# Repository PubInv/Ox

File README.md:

# NASA-COG

## Final Report

The final report delivered to NASA for this project can be [read here](https://drive.google.com/file/d/1jfJcSLfsybuC49I7llPhfTNI8ucRUW3h/view?usp=sharing).

## Introduction

This is a repo for a control system made for NASA to drive a Ceramic Oxygen Generation
technology they have developed. It was forked from ["The Ox"]() project of Public Invention run by Mr. Ben Coombs, which was in turn a fork of the VentOS project of Helpful Engineering let my Ben Coombs, Dr. Erich Schulz, and Robert L. Read.

However, the main reason we are starting with this fork is not that the Pressure Swing
Adsorption system of the Ox is a particularly relevant, but rather that the code
represents a nice platform of simple microcontroller control of related machines.

To wit, includes PlatformIO configuration, a state machine (finite automata),
a superloop architecutre, and a hardware abstraction layer.

This particular project of NASA will improve life support technology in space,
but may eventually greatly improve global health.

An unlisted [YouTube video](https://youtu.be/1nq-Mw7jZ5A) has been uploaded that shows this work in progress as of September, 2022.

## How to run

### Linux
The fundamental way to run this is to perform:  
> cd firmware  
> pio run -e native && ./.pio/build/native/program  
We are currently creating the [RibbonFish](https://github.com/PubInv/NASA-COG/blob/develop/RibbonFish.md) proof-of-concept.
This can be run on a Due by executing:  
> make pio-run-due_ribbonfish  
As this develops, it will use a specific Due hardware configuration,  
please see the [documentation](https://github.com/PubInv/NASA-COG/blob/develop/RibbonFish.md) for details to build your own.  

### Windows
With Visual Studio Code.  
Install the Plateform IO extention  
To open he project in Visual Studio Code.  
Open Project. Navigate to the firmware folder.   
Select the file platformio.ini  

## Annoyances

AFAIK, PlatformIO forces a directory tree depth of 5 levels.

This is not enough to organize the Hardware Abstraction Level they way I would prefer, forcing us to make some messy directories that are less than clear.

For example, to implement a Temperature Sensor, we would ideally have an
abstract (or virtual) implementation, a folder for real hardware,
and a folder for mock sensors.  I have no choice now but to jam
the mock sensors into the same directory with the real hardware and
use a naming convnention.

## The Command System

The NASA-COG system needs to allow the user to enter commands. The most obvious of these is "turn off".
Because the system should avoid thermal shocks, this is actually not simple.

We have previously used an [approach](https://github.com/PubInv/PIRCS-pubinv-respiration-control-standard) of using simple JSON objects to represent commands. We propose to use the same idea here, but obviously,
the command will be custom to the NASA-COG.

### Parameter Setting Commands
The general scheme is to use a JSON object like:

```JavaScript
{ "com": "T",
  "par": 7,
  "mod": "T",
  "val" : 732.3
  }
```

1. "com" is the command. For example, "T" can mean "set Temperature".
2. "par" is a parameter used to specify something about how to execute the command. For example, 7 could mean location 7, which might be between the 6th and 7th stack.
3. "mod" is a modifier of the command. For example, the "set Temperature" command could be used to
set the minimum, maximum, or the target temperature.
4. "val" is the value that is to be set.

For this problem space, we can specify some global parameters of the problem, some of which
involve safety. These can of course have default values "hard wired" into the code, but an
experimenter may wish to change these values (carefully).

1. The maximum rate of voltage change applied to a stack. Nominally we have defined this as 1 volt/second.
We have evidence that too rapid a voltage change (such as that caused by pulse-width modulation) can destroy
a stack.
2. The maximum rate of temperature change for a stack. Nominally we may say this as 2 degree K per minute,
which would allow the machine to reach operating temperature in 6 hours.
3. The maximum temperature difference across a stack in any dimenstion. We may not be able to control
this directly, but we can use it as a target.
4. The maximum voltage applied to a stack.
5. The maximum amperage applied to a stack.

### Event-like Commands

We will need other commands that represent discrete events in time. For example, each transition in the
state transition diagram below may be initiated by a command from the user (they may also occur
automatically due to an internal fault or even normal operation.)

We can implement particular commands with the same scheme.

For example, the simple object:

```JavaScript
{ "com": "C",
  "par": 0,
  "int": "s",
  "mod": "U",
  "val" : 0.0
  }
```

Could mean "Cool Down". The value "U" is used becasue the "mod" command is "unusued" in this case.

```JavaScript
{ "com": "W",
  "par": M,
  "int": "s",
  "mod": "U",
  "val" : 0.0
  }
```

In actual practice, these commands will be pasted into the serial port using either PlatformIO or the Arduino IDE.

Eventually, a user interface may be implemented that uses a knob or a nice webpage to enter commands.
However, by having each of these take only actions that can be implemented as such a command,
we bring discipline to the internal code.

## Actual Serial Commands

The serial port currently supports 6 one-character commands: w,c,e,a,i,o.
These mean:
1. warmup
2. cool down
3. emergency shutdown
4. acknowledge
5. idle
6. operate

Note: "acknowledge" means that the operator acknowledges that a critical
state has occurred and asserts it is okay to return to normal operation,
either because the problem as been removed or for some other reason.

Addtionally, the system supports "full commands", that look like this:

> { "com": "W", "par": "M", "int": "s", "mod": "U", "val" : 0.0 }

> { "com": "C", "par": "M", "int": "s", "mod": "U", "val" : 0.0 }

> { "com": "E", "par": "M", "int": "s", "mod": "U", "val" : 0.0 }

> { "com": "A", "par": "M", "int": "s", "mod": "U", "val" : 0.0 }

> { "com": "I", "par": "M", "int": "s", "mod": "U", "val" : 0.0 }

> { "com": "O", "par": "M", "int": "s", "mod": "U", "val" : 0.0 }

In fact, each "one character" command is a short hand for these commands.

The following format can be used to set parameters (P).
The three most important parameters are:
1. T : Temperature (in C) going into the stack
2. C : Current (in milliamps) going into the stack
3. F : Fan speed in RPM (we expect this to change to flow rate in SLM)
> { "com": "P", "par": "T", "int": "T", "mod": "U", "val" : 35 }

> { "com": "P", "par": "C", "int": "T", "mod": "U", "val" : 500 }

> { "com": "P", "par": "F", "int": "T", "mod": "U", "val" : 2000 }

These three commands set the:
1. Temperature into the stack to 35C
2. Set the Target current into the stack to 500 milliamps
3. Set the flow rate to 2000 ml/seconds

## License

In general we intend to follow the [Public Invention Licensed Guidelines](https://github.com/PubInv/PubInv-License-Guidelines) unless
NASA requests something different. If you are starting your own project, please
feel free to fork the license guidelines as a starting point if you like our
license policy.

This program includes free software: you can redistribute it and/or modify it under the terms of the GNU Affero General Public License as published by the Free Software Foundation, either version 3 of the License, or (at your option) any later version.

See the GNU Affero General Public License for more details. You should have received a copy of the GNU Affero General Public License along with this program. If not, see <https://www.gnu.org/licenses/>.

This program is distributed in the hope that it will be useful, but WITHOUT ANY WARRANTY; without even the implied warranty of MERCHANTABILITY or FITNESS FOR A PARTICULAR PURPOSE.

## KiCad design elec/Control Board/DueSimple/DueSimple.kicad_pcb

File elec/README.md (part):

# Electrical Information on ODECOS Controler(s) and Plant(s)
PCB Connector Pin signal names, Due Signal Names, Chassis wiring and related information
Inverse cronological order

## Unit 3-???
A place holder for future work
See: TBD

## Unit 2
### Notes for creation of a new PCB  
This table pulls from information in the references 1 and 2.   
References:
1. Due Pin-Out Map for OEDCS1 : https://docs.google.com/spreadsheets/d/18wP1Cyg5-j3FP92x7no_JsCCFNvo9y2avyn5nvmAj6I/edit#gid=0
2. Fan Controller and Fan Wiring for OEDCS1: https://docs.google.com/document/d/1n3v-AxqNKEzcKqmHicGKnFmG8sKbNEL_pGaUlU9CZ8U/edit

   WARNING! At present pin D4 works without an external pull up resistor for the termocouples, but D5 does not; it requires an external pull up resistor
   Until we have time to rework our perf board, I am going to continue to use D4 for the MAX31850 OneWire interface.

#### Due Pin Wiring
| **Due Pin Number** 	| **Breakout** 	| **Signal Name** 	| **Set as I/O**   	| **Connection**                      	| **Notes**                             	|
|--------------------	|--------------	|-----------------	|------------------	|-------------------------------------	|---------------------------------------	|
| D0                 	| J6-2         	| NA              	| Input pullup.    	| None                                	| Not used                              	|
| D1                 	| J6-1         	| NA              	| Input pullup.    	| None                                	| Not used                              	|
| D2                 	| J6-3         	| NA              	| Input pullup.    	| None                                	| Not used                              	|
| D3                 	| J6-4         	| NA              	| Input pullup.    	| None                                	| Not used                              	|
| D4                 	| J6-5         	| SD ENABLE (BUT ALSO TEMP1) | Input pullup.    	| None                      	| SD CS on Ethernet card.               	|
| D5                 	| J6-6         	| TEMP1           	| BiDirection      	| Dallas 1 Wire / MAX31850K           	| Three daisy chained, requires 4.7k ohm pull up resistor (but D4 does not!) Please see note                   	|
| D6                 	| J6-7         	| NA              	| Input pullup.    	| None                                	| Not used                              	|
| D7                 	| J6-8         	| NA              	| Input pullup.    	| None                                	| Not used                              	|
| D8                 	| J7-1         	| NA              	| Input pullup.    	| None                                	| Not used                              	|
| D9                 	| J7-2         	| nFAN1_PWM       	| Output           	| Controlles transistor Q1            	| Was BLOWER_PWM                        	|
| D10                	| J7-3         	| NA              	| Input pullup.    	| None                                	| Not used                              	|
| D11                	| J7-4         	| NA              	| Input pullup.    	| None                                	| Not used                              	|
| D12                	| J7-5         	| NA              	| Input pullup.    	| None                                	| Not used                              	|
| D13                	| J7-6         	| NA              	| Input pullup.    	| None                                	| Not used                              	|
| D13                	| J7-6         	| NA              	| Input pullup.    	| None                                	| Not used                              	|
| D14                	| J2-1         	| NA              	|                  	| None                                	| Not used                              	|
| D15                	| J2-2         	| NA              	| Input pullup.    	| None                                	| Not used                              	|
| D16                	| J2-3         	| NA              	| Input pullup.    	| None                                	| Can be TX2                            	|
| D17                	| J2-4         	| NA              	| Input pullup.    	| None                                	| Can be RX2                            	|
| D18                	| J2-5         	| D_PSU_TX        	| UART1 TX         	| D_PSU_TX, R15 (then to Power Supply 	| TX1                                   	|
| D19                	| J2-6         	| D_PSU_RX        	| UART1 RX         	| D_PSU_RX, R14 (then to Power Supply 	| RX1                                   	|
| D20                	| J2-7         	| SDA             	| SDA              	| test point SDA1, R4, R13            	| SDA                                   	|
| D21                	| J2-8         	| SCL             	| SCL              	| test point SCL1, R2, R16            	| SCL                                   	|
| D22                	| J8-4         	| BLOWER_ENABLE   	| OUTPUT           	| R10                                 	| Enable Switched_Fan_Power at J15 9-12 	|
| D23                	| J8-3         	| NA              	| Input pullup.    	| None                                	| Not used                              	|
| D24                	| J8-6         	| NA              	| Input pullup.    	| None                                	| Not used                              	|
| D25                	| J8-5         	| NA              	| Input pullup.    	| None                                	| Not used                              	|
| D26                	| J8-8         	| NA              	| Input pullup.    	| None                                	| Not used                              	|
| D27                	| J8-7         	| NA              	| Input pullup.    	| None                                	| Not used                              	|
| D28                	| J8-10        	| NA              	| Input pullup.    	| None                                	| Not used                              	|
| D29                	| J8-9         	| NA              	| Input pullup.    	| None                                	| Not used                              	|
| D30                	| J8-12        	| NA              	| Input pullup.    	| None                                	| Not used                              	|
| D31                	| J8-11        	| NA              	| Input pullup.    	| None                                	| Not used                              	|
| D32                	| J8-14        	| nCS_GPAD        	| Output for nCS   	| R55, R61, Q5                        	| on 3.3 Volt                           	|
| D33                	| J8-13        	| TC_nCS1         	| Output for nCS   	| Thermocouple 1, R7                  	| on 3.3 Volt                           	|
| D34                	| J8-16        	| TC_nCS2         	| Output for nCS   	| Thermocouple 2, R3                  	| on 3.3 Volt                           	|
| D35                	| J8-15        	| TC_nCS3         	| Output for nCS   	| Thermocouple 3, R1                  	| on 3.3 Volt                           	|
| D36                	| J8-18        	| NA              	| Input pullup.    	| None                                	| Not used                              	|
| D37                	| J8-17        	| NA              	| Input pullup.    	| None                                	| Not used                              	|
| D38                	| J8-20        	| NA              	| Input pullup.    	| None                                	| Not used                              	|
| D39                	| J8-19        	| NA              	| Input pullup.    	| None                                	| Not used                              	|
| D39                	| J8-19        	| NA              	| Input pullup.    	| None                                	| Not used                              	|
| D40                	| J8-22        	| NA              	| Input pullup.    	| None                                	| Not used                              	|
| D41                	| J8-21        	| NA              	| Input pullup.    	| None                                	| Not used                              	|
| D42                	| J8-24        	| NA              	| Input pullup.    	| None                                	| Not used                              	|
| D43                	| J8-23        	| NA              	| Input pullup.    	| None                                	| Not used                              	|
| D44                	| J8-26        	| NA              	| Input pullup.    	| None                                	| Not used                              	|
| D45                	| J8-25        	| NA              	| Input pullup.    	| None                                	| Not used                              	|
| D46                	| J8-28        	| NA              	| Input pullup.    	| None                                	| Not used                              	|
| D47                	| J8-27        	| NA              	| Input pullup.    	| None                                	| Not used                              	|
| D48                	| J8-30        	| NA              	| Input pullup.    	| None                                	| Not used                              	|
| D49                	| J8-29        	| NA              	| Input pullup.    	| None                                	| Not used                              	|
| D50                	| J8-32        	| NA              	| Input pullup.    	| None                                	| Not used                              	|
| D51                	| J8-31        	| SSR_PWM         	| OUTPUT           	| R9                                  	| Active High.                          	|
| D52                	| J8-34        	| NA              	| Input pullup.    	| None                                	| Not used                              	|
| D53                	| J8-33        	| NA              	| Input pullup.    	| None                                	| Not used                              	|
| SDA1               	| J7-9         	| NA              	| Input pullup.    	| None                                	| Not used                              	|
| SCL1               	| J7-10        	| NA              	| Input pullup.    	| None                                	| Not used                              	|
| CANR               	| J4-7         	| NA              	| Input pullup.    	| None                                	| Not used                              	|
| CANT               	| J4-8         	| NA              	| Input pullup.    	| None                                	| Not used                              	|
| DAC0               	| J4-5         	| Disable         	| Only Output      	| None                                	| Not used                              	|
| DAC1               	| J4-6         	| Disable         	| Only Output      	| None                                	| Not used                              	|
| A0                 	| J5-1         	| BLOWER_TACH     	| Input pullup.    	| R11                                 	| Measure RPM                           	|
| A1                 	| J5-2         	| NA              	| Input pullup.    	| None                                	| Not used                              	|
| A2                 	| J5-3         	| NA              	| Input pullup.    	| None                                	| Not used                              	|
| A3                 	| J5-4         	| NA              	| Input pullup.    	| None                                	| Not used                              	|
| A4                 	| J5-5         	| NA              	| Input pullup.    	| None                                	| Not used                              	|
| A5                 	| J5-6         	| NA              	| Input pullup.    	| None                                	| Not used                              	|
| A6                 	| J5-7         	| NA              	| Input pullup.    	| None                                	| Not used                              	|
| A7                 	| J5-8         	| NA              	| Input pullup.    	| None                                	| Not used                              	|
| A8                 	| J4-1         	| NA              	| Input pullup.    	| None                                	| Not used                              	|
| A9                 	| J4-2         	| NA              	| Input pullup.    	| None                                	| Not used                              	|
| A9                 	| J4-2         	| NA              	| Input pullup.    	| None                                	| Not used                              	|
| A10                	| J4-3         	| NA              	| Input pullup.    	| None                                	| Not used                              	|
| A11                	| J4-4         	| NA              	| Input pullup.    	| None                                	| Not used                              	|
| AREF               	| J7-8         	| NA              	| From DUE         	| None                                	| Not used                              	|
| nRST1              	| J3-6         	| NA              	| Pulled up on DUE 	| None                                	| Not used                              	|
| IOREF              	| J3-7         	| NA              	| NA               	| None                                	| Not used                              	|
| VIN                	| J3-1         	| VIN             	| NA               	| +12V into this pin through R76      	|                                       	|
| +5V                	| J3-4         	| VIN+5V          	| NA               	| Power from Due voltage regulator    	| Three pins.                           	|
| 3.3V               	| J3-5         	| 3.3V            	| NA               	| Power from Due voltage regulator    	| One pin.                              	|
| MISO               	| tp CPIO1     	| CIPO            	| Input            	| SPI bus                             	|                                       	|
| MOSI               	| tp COPI      	| COPI            	| Output           	| SPI bus                             	|                                       	|
| SCK                	| tp SPI_SCK   	| SPI_SCK         	| Output           	| SPI bus                             	|                                       	|
| nRST2              	| NA           	| SPI_nRST        	| Input            	| S1 reset switch                     	|                                       	|
| end                	|              	|                 	|                  	|                                     	|                                       	|  

**Ethernet pin usage:**
Pins usage on Arduino
* D4: SD card chip select
* D10: W5200 Chip Select
* D11: SPI MOSI
* D12: SPI MISO
* D13: SPI SCK

### Chassis Wiring of ODECOS Unit 2.
Diagram(s) here...

## Unit 1
Wiring of ODECOS Unit 1 Notes
1. Due Pin-Out Mape for OEDCS1 : https://docs.google.com/spreadsheets/d/18wP1Cyg5-j3FP92x7no_JsCCFNvo9y2avyn5nvmAj6I/edit#gid=0
2. Fan Controller and Fan Wiring for OEDCS1: https://docs.google.com/document/d/1n3v-AxqNKEzcKqmHicGKnFmG8sKbNEL_pGaUlU9CZ8U/edit

Wiring of thermocouple amplifires

Revisions:
* 20230821, Update DB25 Male 2-5 from +12V to "+24V Switched (fans)"

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
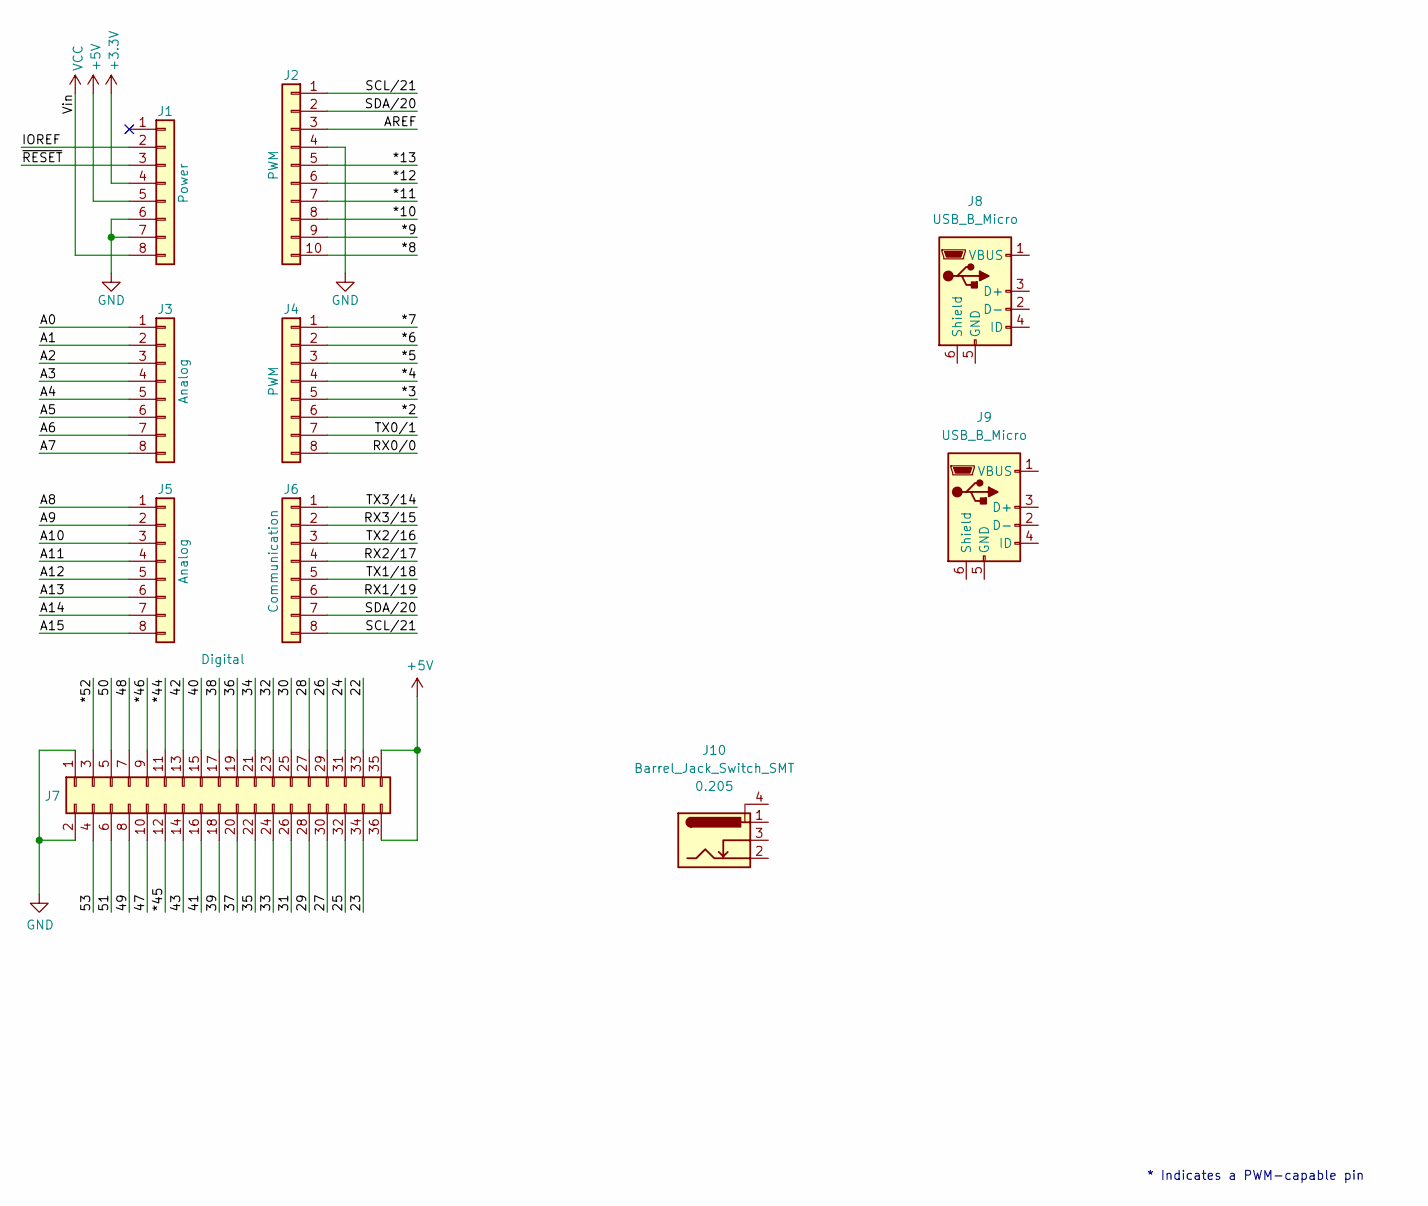
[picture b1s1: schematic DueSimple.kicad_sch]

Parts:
J1: Power; PinSocket_1x08_P2.54mm_Vertical
J2: PWM; PinSocket_1x10_P2.54mm_Vertical
J3, J5: Analog; PinSocket_1x08_P2.54mm_Vertical
J4: PWM; PinSocket_1x08_P2.54mm_Vertical
J6: Communication; PinSocket_1x08_P2.54mm_Vertical
J7: Digital; PinSocket_2x18_P2.54mm_Vertical
J8, J9: USB_B_Micro; USB_Micro-B_Molex-105017-0001
J10: Barrel_Jack_Switch_SMT; BarrelJack_CLIFF_FC681465S_SMT_Horizontal; MPN DC-005-5A-2.0-SMT / 54-00164

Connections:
+3V3: J1.4
+5V: J1.5, J7.35, J7.36
/22: J7.33
/23: J7.34
/24: J7.31
/25: J7.32
/26: J7.29
/27: J7.30
/28: J7.27
/29: J7.28
/30: J7.25
/31: J7.26
/32: J7.23
/33: J7.24
/34: J7.21
/35: J7.22
/36: J7.19
/37: J7.20
/38: J7.17
/39: J7.18
/40: J7.15
/41: J7.16
/42: J7.13
/43: J7.14
/47: J7.10
/48: J7.7
/49: J7.8
/50: J7.5
/51: J7.6
/53: J7.4
/*2: J4.6
/*3: J4.5
/*4: J4.4
/*5: J4.3
/*6: J4.2
/*7: J4.1
/*8: J2.10
/*9: J2.9
/*10: J2.8
/*11: J2.7
/*12: J2.6
/*13: J2.5
/*44: J7.11
/*45: J7.12
/*46: J7.9
/*52: J7.3
/A0: J3.1
/A1: J3.2
/A2: J3.3
/A3: J3.4
/A4: J3.5
/A5: J3.6
/A6: J3.7
/A7: J3.8
/A8: J5.1
/A9: J5.2
/A10: J5.3
/A11: J5.4
/A12: J5.5
/A13: J5.6
/A14: J5.7
/A15: J5.8
/AREF: J2.3
/IOREF: J1.2
/RX0/0: J4.8
/RX1/19: J6.6
/RX2/17: J6.4
/RX3/15: J6.2
/SCL/21: J2.1, J6.8
/SDA/20: J2.2, J6.7
/TX0/1: J4.7
/TX1/18: J6.5
/TX2/16: J6.3
/TX3/14: J6.1
/~RESET: J1.3
GND: J1.6, J1.7, J2.4, J7.1, J7.2
VCC: J1.8

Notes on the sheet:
* Indicates a PWM-capable pin

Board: 2 copper layers, 16 parts (0 on the bottom side), 4 nets, no tracks yet.

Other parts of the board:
MH1, MH2, MH3, MH4, MH5, MH6: MountingHole_3.2mm

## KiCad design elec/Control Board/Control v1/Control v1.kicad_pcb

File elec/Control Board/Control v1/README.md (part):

# Control V1
Version 1 control board for NASA COG
On line schematic viewing from **Kicanvas** See: https://kicanvas.org  
The Control V1 is an Arduino DUE "Shield". The DUE will live below this printed wiring assembly. An Ethernet shield will live above as a "Socket". See KiCad Symbol & Footprint Library for Arduino Modules for "Shield" and "Socket"

## Schematics
### Browser page view of the schematic by KiCanvas.org 
Top page is "Control v1.kicad_sch". Note the page for MAX31856 is actualy for an MCP9600 but the page was not renamed (as of 20230830)
*  [Control v1.kicad_sch](https://kicanvas.org/?github=https%3A%2F%2Fgithub.com%2FPubInv%2FNASA-COG%2Fblob%2Fdevelop%2Felec%2FControl%2520Board%2FControl%2520v1%2FControl%2520v1.kicad_sch)
* [Adafruit-MAX31850-thermocouple-breakout-board.kicad_sch](https://kicanvas.org/?github=https%3A%2F%2Fgithub.com%2FPubInv%2FNASA-COG%2Fblob%2Fdevelop%2Felec%2FControl%2520Board%2FControl%2520v1%2FAdafruit-MAX31850-thermocouple-breakout-board.kicad_sch)
* [Adafruit-MAX31855-breakout-board.kicad_sch](https://kicanvas.org/?github=https%3A%2F%2Fgithub.com%2FPubInv%2FNASA-COG%2Fblob%2Fdevelop%2Felec%2FControl%2520Board%2FControl%2520v1%2FAdafruit-MAX31855-breakout-board.kicad_sch)
* [Adafruit-MAX31856-PCB-master.kicad_sch](https://kicanvas.org/?github=https%3A%2F%2Fgithub.com%2FPubInv%2FNASA-COG%2Fblob%2Fdevelop%2Felec%2FControl%2520Board%2FControl%2520v1%2FAdafruit-MAX31856-PCB-master.kicad_sch)
* [Fan controller.kicad_sch](https://kicanvas.org/?github=https%3A%2F%2Fgithub.com%2FPubInv%2FNASA-COG%2Fblob%2Fdevelop%2Felec%2FControl%2520Board%2FControl%2520v1%2FFan%2520controller.kicad_sch)
* [I2C_Level_Shifter.kicad_sch](https://kicanvas.org/?github=https%3A%2F%2Fgithub.com%2FPubInv%2FNASA-COG%2Fblob%2Fdevelop%2Felec%2FControl%2520Board%2FControl%2520v1%2FI2C_Level_Shifter.kicad_sch)
* [SPI_ControllerLevel_Shifter.kicad_sch](https://kicanvas.org/?github=https%3A%2F%2Fgithub.com%2FPubInv%2FNASA-COG%2Fblob%2Fdevelop%2Felec%2FControl%2520Board%2FControl%2520v1%2FSSR%2520Interface.kicad_sch)
* [SSR Interface.kicad_sch](https://kicanvas.org/?https%3A%2F%2Fgithub.com%2FPubInv%2FNASA-COG%2Fblob%2Fdevelop%2Felec%2FControl+Board%2FControl+v1%2FSSR+Interface.kicad_sch=&github=https%3A%2F%2Fgithub.com%2FPubInv%2FNASA-COG%2Fblob%2Fdevelop%2Felec%2FControl%2520Board%2FControl%2520v1%2FSSR%2520Interface.kicad_sch)

## PCB / PWA
### Browser page view of the PCB by KiCanvas.org 
Printed Circuit Board, Printed Wiring Assembly
* [Control v1.kicad_pcb](https://kicanvas.org/?https://github.com/ForrestErickson/NASA-COG/blob/develop/elec/Control%20Board/Control%20v1/Control%20v1.kicad_pcb](https://kicanvas.org/?https%3A%2F%2Fgithub.com%2FForrestErickson%2FNASA-COG%2Fblob%2Fdevelop%2Felec%2FControl+Board%2FControl+v1%2FControl+v1.kicad_pcb=&github=https%3A%2F%2Fgithub.com%2FForrestErickson%2FNASA-COG%2Fblob%2Fdevelop%2Felec%2FControl%2520Board%2FControl%2520v1%2FControl%2520v1.kicad_pcb))

### PCB / PWA 3D Snapshot

File Notes:
Add BOM spread sheet and a JLCPCB BOM.  The instructions / notes for generating the BOM and JLCPCB BOM are embedded in the file, Control_V1_BOM.xls. The proccess starts in KiCad with the BOM gewnerator nick name, "bom_csv_grouped_by_value"
* Control_V1_BOM.xls
* Control_V1_BOM_JLCPCB_20230829_2137.csv

## License, Public Invention for this PCB, PWA
* [Firmware: Affero GPL 3.0](https://www.gnu.org/licenses/agpl-3.0.en.html#license-text)
* [CERN Open Hardware Licence Version 2 - Strongly Reciprocal](https://ohwr.org/cern_ohl_s_v2.txt)
<hr> 

## KiCad Symbol & Footprint Library for Arduino Modules
<a href="./PICS/Rev2/PWA_FrontView.png">  
*Version 4.1.0*  

This is a library of KiCad schematic symbols and PCB footprints for most Arduino modules. You can use them to make your own PCB design which will effortlessly connect with your chosen Arduino module.

Currently included modules:
- Arduino **101** Shield
- Arduino **Due** Shield
- Arduino **Giga R1 WiFi** Shield
- Arduino **Leonardo** Shield
- Arduino **M0** Shield
- Arduino **M0 Pro** Shield
- Arduino **Mega 2560 R3** Shield
- Arduino **Micro** Socket
- Arduino **Mini** Socket
- Arduino **MKR 1000 WiFi** Socket
- Arduino **MKR WiFi 1010** Socket
- Arduino **MKR FOX 1200** Socket
- Arduino **MKR WAN 1300** Socket
- Arduino **MKR WAN 1310** Socket
- Arduino **MKR GSM 1400** Socket
- Arduino **MKR NB 1500** Socket
- Arduino **MKR Vidor 4000** Socket
- Arduino **MKR Zero** Socket
- Arduino **Nano** Socket
- Arduino **Nano 33 BLE** Socket / Tile
- Arduino **Nano 33 BLE Sense** Socket / Tile
- Arduino **Nano 33 BLE Sense R2** Socket / Tile
- Arduino **Nano 33 IoT** Socket / Tile
- Arduino **Nano Every** Socket / Tile
- Arduino **Nano RP2040 Connect** Socket / Tile
- Arduino **Nicla Sense ME** Socket / Tile
- Arduino **Nicla Vision** Socket / Tile
- Arduino **Nicla Voice** Socket / Tile
- Arduino **Pro Mini** Socket
- Arduino **Uno R1** Shield
- Arduino **Uno R2** Shield
- Arduino **Uno R3** Shield
- Arduino **Uno R3 SMD** Shield
- Arduino **Uno R4 Minima** Shield
- Arduino **Uno R4 WiFi** Shield
- Arduino **Uno WiFi R2** Shield
- Arduino **Zero** Shield
- Clone **Mega 2560 Pro** Socket
- Clone **Pro Mini** Socket

*"Shield" means the module is designed to plug in from beneath your PCB. "Socket" means the module is designed to plug in from above your PCB. "Tile" means the module is designed to be soldered directly on to your PCB using surface-mount pads.*

## KiCad Version Compatibility
This library requires at least KiCad 6 to function, and is tested on KiCad versions 6.0.8 and 7.0.2. Note that the installation procedure is different for KiCad 6 and 7; please see the [Library Installation](#library-installation) section below.

## Comments, Requests, Bugs & Contributions
All are welcome!
Please open an [Issue](https://github.com/Alarm-Siren/arduino-kicad-library/issues) or [Pull Request](https://github.com/Alarm-Siren/arduino-kicad-library/pulls), as appropriate.

## Library Installation
To install this library in your copy of KiCad, choose the correct section for your version of KiCad and follow the steps given. These instructions only cover automated installation using KiCad's built-in Package and Content Manager (PCM); manual installation is possible but not supported.

### KiCad 7

**Warning**: Do not change the nickname prefix from that given in step 4 below. If you do so KiCad will not assign the correct footprints to the symbols by default.

1. Open KiCad and open the Preferences window at "Preferences" -> "Preferences..."
2. Select the "Plugin and Content Manager" section in the left-hand pane.
3. Ensure that the "Automatically add installed libraries to the global lib table" option is ticked.
4. Ensure that the "Library nickname prefix" is set to "PCM_".
5. Ensuring that the "Check for package updates on startup" option is ticked is recommended. **(Optional)**
6. Click "OK" to close the Preferences window.
7. Click the "Plugin and Content Manager" button.
8. Select the "KiCad official repository" from the top drop-down box (if not already selected).
9. Go the Libraries tab and locate the "KiCad Library for Arduino Modules" in the list.
10. Click the "Install" button for that entry in the list.
11. Click "Apply Pending Changes".
12. Close the "Applying Package Changes" window once it has finished.
13. You should now find that this library is listed in the "Installed" tab.
14. Close the Plugin and Content Manager.
15. You may need to restart KiCad for the library installation to fully take effect. **(Optional)**
16. All done: you are now ready to use these schematic components and footprints in your projects!

### KiCad 6
**Recommendation:** If you can, you should upgrade to KiCad 7.

**Warning**: Do not change the Nicknames from those given in steps 12 and 18 below. If you do so KiCad will not assign the correct footprints to the symbols by default.

1. Open KiCad and click the "Plugin and Content Manager" button.
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
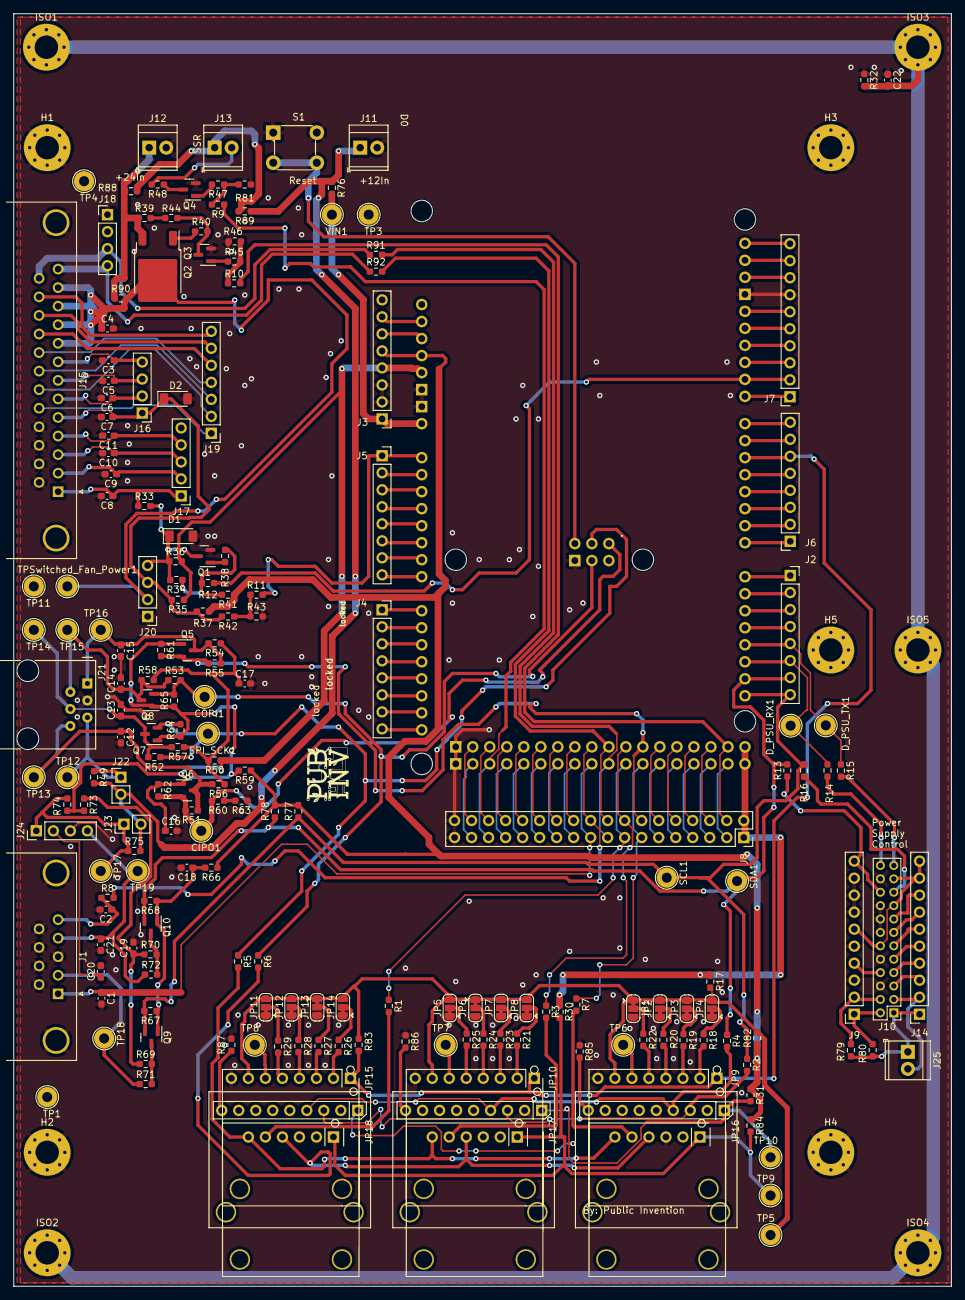
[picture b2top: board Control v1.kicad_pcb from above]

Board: 2 copper layers, 140.0 x 190.0 mm, 211 parts (0 on the bottom side), 191 nets.

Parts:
A1: Arduino_Due_Shield
C1, C2, C12, C13, C14, C15, C20, C21: 39PF; C_0603_1608Metric_Pad1.08x0.95mm_HandSolder
C3, C4, C5, C6, C7, C8, C9, C10, C11: 39pF; C_0603_1608Metric_Pad1.08x0.95mm_HandSolder
C16, C17, C18, C19: 1uF; C_0603_1608Metric_Pad1.08x0.95mm_HandSolder
C22: 10nF; C_0603_1608Metric_Pad1.08x0.95mm_HandSolder
CIPO1: CIPO; TestPoint_Loop_D2.54mm_Drill1.5mm_Beaded
COPI1: COPI; TestPoint_Loop_D2.54mm_Drill1.5mm_Beaded
D1, D2: DNI; D_MiniMELF
D_PSU_RX1: D_PSU_RX; TestPoint_Loop_D2.54mm_Drill1.5mm_Beaded
D_PSU_TX1: D_PSU_TX; TestPoint_Loop_D2.54mm_Drill1.5mm_Beaded
H1, H2, H3, H4, H5: MountingHole_Pad_3.5mm; MountingHole_3.5mm_Pad_Via
ISO1, ISO2, ISO3, ISO4, ISO5: MountingHole_Pad_3.5mm; MountingHole_3.5mm_Pad_Via
J1: DB9_Female_MountingHoles; DSUB-9_Female_Horizontal_P2.77x2.84mm_EdgePinOffset4.94mm_H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
J2, J4, J5, J6: Conn_01x08; PinSocket_1x08_P2.54mm_Vertical
J3: Conn_01x08; PinHeader_1x08_P2.54mm_Vertical
J7, J9, J14: Conn_01x10; PinSocket_1x10_P2.54mm_Vertical
J8: Conn_02x18_Odd_Even; PinSocket_2x18_P2.54mm_Vertical
J10: Conn_02x12_Odd_Even; PinHeader_2x12_P2.00mm_Vertical
J11, J12, J13, J25: Screw_Terminal_01x02; TerminalBlock_TE_282834-2_1x02_P2.54mm_Horizontal
J15: DB25_Female_MountingHoles; DSUB-25_Female_Horizontal_P2.77x2.84mm_EdgePinOffset4.94mm_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
J16, J18, J20, J24: Conn_01x04; PinHeader_1x04_P2.54mm_Vertical
J17: Conn_01x05; PinHeader_1x05_P2.54mm_Vertical
J19: Conn_01x07; PinHeader_1x07_P2.54mm_Vertical
J21: RJ12_6P6C_HORZ; RJ12_Amphenol_54601
J22, J23: 0.100_2Pin; PinHeader_1x02_P2.54mm_Vertical
JP1, JP2, JP3, JP4, JP5, JP6, JP7, JP8, JP11, JP12, JP13, JP14: SolderJumper_3_Bridged12; SolderJumper-3_P1.3mm_Bridged12_RoundedPad1.0x1.5mm
JP9, JP10, JP15: MAX31850K; Adafruit_MAX31850K_Module
JP16, JP17, JP18: MAX31855; Adafruit_MAX31855_Module
JP19, JP21: MCP9600; Adafruit_MCP9600_Module
JP20: MCP9600_; Adafruit_MCP9600_Module
Q1, Q3, Q4, Q5, Q6, Q7, Q8, Q9, Q10: BSS138; SOT-23
Q2: NCE01P30K; TO-252-2
R1, R2, R3, R4, R5, R6, R7, R8, R13, R14, R15, R16, R31, R33, R48, R76, R79, R80, R82, R84, R88: 1R0; R_0603_1608Metric_Pad0.98x0.95mm_HandSolder
R9, R10, R11, R12, R49, R50, R59, R66, R73, R91, R92: 1R; R_0603_1608Metric_Pad0.98x0.95mm_HandSolder
R17, R30, R34, R35, R43, R51, R52, R53, R55, R60, R63, R74, R75, R85, R86, R87, R89, R90: DNI; R_0603_1608Metric_Pad0.98x0.95mm_HandSolder
R18, R19, R20, R21, R22, R23, R24, R25, R26, R27, R28, R29, R36, R37, R38, R42, R45, R47, R54, R57, R58, R62: 1K; R_0603_1608Metric_Pad0.98x0.95mm_HandSolder
R32: 4M7; R_0603_1608Metric_Pad0.98x0.95mm_HandSolder
R39, R40, R41, R44, R46, R56, R61, R64, R65, R67, R68, R69, R70, R81: 10K; R_0603_1608Metric_Pad0.98x0.95mm_HandSolder
R71, R72: 39R; R_0603_1608Metric_Pad0.98x0.95mm_HandSolder
R77, R78, R83: 4K7; R_0603_1608Metric_Pad0.98x0.95mm_HandSolder
S1: SWITCH_TACTILE_SPST-NO_0.05A_24V; Switch_Tactile_THT_6x6mm
SCL1: SCL; TestPoint_Loop_D2.54mm_Drill1.5mm_Beaded
SDA1: SDA; TestPoint_Loop_D2.54mm_Drill1.5mm_Beaded
SPI_SCK1: SPI_SCK; TestPoint_Loop_D2.54mm_Drill1.5mm_Beaded
TP1, TP3, TP4, TP11: GND; TestPoint_Loop_D2.54mm_Drill1.5mm_Beaded
TP5: +VccMAX31850; TestPoint_Loop_D2.54mm_Drill1.5mm_Beaded
TP6: +VccMAX31850_1; TestPoint_Loop_D2.54mm_Drill1.5mm_Beaded
TP7: +VccMAX31850_2; TestPoint_Loop_D2.54mm_Drill1.5mm_Beaded
TP8: +VccMAX31850_3; TestPoint_Loop_D2.54mm_Drill1.5mm_Beaded
TP9: +VccMAX3185; TestPoint_Loop_D2.54mm_Drill1.5mm_Beaded
TP10: +VccMCP9600; TestPoint_Loop_D2.54mm_Drill1.5mm_Beaded
TP12: ControllerVCC; TestPoint_Loop_D2.54mm_Drill1.5mm_Beaded
TP13: CPIO; TestPoint_Loop_D2.54mm_Drill1.5mm_Beaded
TP14: SCK; TestPoint_Loop_D2.54mm_Drill1.5mm_Beaded
TP15: COPI; TestPoint_Loop_D2.54mm_Drill1.5mm_Beaded
TP16: nCS; TestPoint_Loop_D2.54mm_Drill1.5mm_Beaded
TP17: I2C_VCC; TestPoint_Loop_D2.54mm_Drill1.5mm_Beaded
TP18: SCL_5V; TestPoint_Loop_D2.54mm_Drill1.5mm_Beaded
TP19: SDA_5V; TestPoint_Loop_D2.54mm_Drill1.5mm_Beaded
TPSwitched_Fan_Power1: Switched_Fan_Power; TestPoint_Loop_D2.54mm_Drill1.5mm_Beaded
VIN1: VIN1; TestPoint_Loop_D2.54mm_Drill1.5mm_Beaded

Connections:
5VHead: A1.5V3 (5V), A1.5V4 (5V), J8.1, J8.2, R17.1, R30.1
+3.3V: A1.3V3 (3.3V), J3.5, R31.1, R37.2, R41.1, R59.1, R66.1, R77.2, R78.2, R82.1, R84.1
+5V: A1.5V1 (5V), J3.4, R35.1, R36.2, R50.1, R73.2, R74.2
+12V: J11.1, J22.2, J23.2, R49.2, R75.2, R76.1, R89.1
+24V: J12.1, Q2.3 (S), R39.1, R88.1, R90.1
/ACI: J10.13, J14.7
/AUX: J9.6, J10.12, J10.17, J10.21, J14.9, J14.10
/Blower controller/FAN1_FG: R11.1, R42.1, R43.1
/Blower controller/FAN_POWER: R10.1, R45.2, R46.1
/Blower controller/LOOPBACK13: J15.13, J18.4, R92.1
/Blower controller/LOOPBACK25: J15.25, J18.3, R91.1
/Blower controller/PWMFan1: C8.1, J15.1, J17.1, R33.1
/Blower controller/PWMFan2: C9.1, J15.2, J17.2
/Blower controller/PWMFan3: C10.1, J15.3, J17.3
/Blower controller/PWMFan4: C11.1, J15.4, J17.4
/Blower controller/Switched_Fan_Power: C4.1, J15.9, J15.10, J15.11, J15.12, J20.2, Q2.2 (D), R90.2, TPSwitched_Fan_Power1.1
/Blower controller/TachFan1: C7.1, D2.1 (K), J15.5, J16.1, J20.3, R35.2, R37.1, R42.2
/Blower controller/TachFan2: C6.1, J15.6, J16.2
/Blower controller/TachFan3: C5.1, J15.7, J16.3
/Blower controller/TachFan4: C3.1, J15.8, J16.4
/Blower controller/nFAN1_PWM: R12.1, R34.1, R38.2, R41.2
/D_PSU_RX: A1.D19 (D19/RX1), D_PSU_RX1.1, J2.6, R14.2
/D_PSU_TX: A1.D18 (D18/TX1), D_PSU_TX1.1, J2.5, R15.1
/EN+: J10.11, J14.6
/EN-: J10.9, J14.5
/I2C_LevelShift/+3V3Local: C18.1, Q9.1 (G), Q10.1 (G), R66.2, R67.1, R68.1
/I2C_LevelShift/+5VLocal: C19.1, R69.1, R70.1, R73.1
/I2C_LevelShift/I2C_VCC: J23.1, J24.1, R74.1, R75.1, TP17.1
/I2C_LevelShift/SCL_5V: C20.1, J1.2, J24.2, R71.1, TP18.1
/I2C_LevelShift/SDA_5V: C21.1, J1.4, J24.4, R72.1, TP19.1
/PAR: J10.7, J14.4
/POK: J10.5, J14.3
/PS_SCL: J10.19, R16.2
/PS_SDA: J9.10, J10.20, R13.1
/RX: J10.23, R15.2
/SPI_ControllerLevel_Shifter/+3V3Local: C16.1, Q5.1 (G), Q6.1 (G), Q7.1 (G), Q8.1 (G), R59.2, R61.1, R62.1, R64.1, R65.1
/SPI_ControllerLevel_Shifter/+5VLocal: C17.1, R50.2, R54.1, R56.1, R57.1, R58.1
/SPI_ControllerLevel_Shifter/CIPO: C12.1, J21.6, Q6.3 (D), R51.1, R56.2, TP13.1
/SPI_ControllerLevel_Shifter/COPI: C14.1, J21.2, Q8.3 (D), R53.1, R58.2, TP15.1
/SPI_ControllerLevel_Shifter/C_SCK: C13.1, J21.4, Q7.3 (D), R52.1, R57.2, TP14.1
/SPI_ControllerLevel_Shifter/ControllerVcc: J21.5, J22.1, R49.1, TP12.1
/SPI_ControllerLevel_Shifter/nCS: C15.1, J21.1, Q5.3 (D), R54.2, R55.1, TP16.1
/SSR Interface/Heater: R9.2, R47.1, R81.1
/SSR Interface/Heater_SSR_High: J13.1, R88.2, R89.2
/SSR Interface/Heater_SSR_Low: J13.2, R48.2
/TX: J10.24, R14.1
/Thermocouple Amplifier I2C breakout board - MCP9600/+VccMCP9600: JP19.1, JP20.1, JP21.1, R31.2, TP10.1
/Thermocouple Amplifier I2C breakout board - MCP9600/SCL: JP19.3, JP20.3, JP21.3, R2.2
/Thermocouple Amplifier I2C breakout board - MCP9600/SDA: JP19.4, JP20.4, JP21.4, R4.2
/Thermocouple Amplifier SPI Interface breakout board - MAX31855 /+VccMAX31855: JP16.1, JP17.1, JP18.1, R30.2, R84.2, TP9.1
/Thermocouple Amplifier SPI Interface breakout board - MAX31855 /DO: JP16.4, JP17.4, JP18.4, R6.2
/Thermocouple Amplifier SPI Interface breakout board - MAX31855 /SCK: JP16.6, JP17.6, JP18.6, R5.2
/Thermocouple Amplifier SPI Interface breakout board - MAX31855 /nCS_1: JP16.5, R7.2
/Thermocouple Amplifier SPI Interface breakout board - MAX31855 /nCS_2: JP17.5, R3.2
/Thermocouple Amplifier SPI Interface breakout board - MAX31855 /nCS_3: JP18.5, R1.2
/Thermocouple Amplifier with 1-Wire Breakout Board - MAX31850K/+VccMAX31850: JP1.1 (A), JP2.3 (B), JP3.3 (B), JP4.3 (B), JP5.3 (B), JP6.1 (A), JP7.3 (B), JP8.3 (B), JP9.7, JP10.7, JP11.3 (B), JP12.3 (B), JP13.1 (A), JP14.3 (B), JP15.7, R17.2, R82.2, R83.2, TP5.1
/VCI: J10.15, J14.8
/VO+: J9.1, J10.2, R80.2
/VO-: J9.2, J10.4, R79.2
/VS+: J10.1, J14.1, J25.1, R79.1, R80.1
/VS-: J10.3, J14.2, J25.2
/VSET: J9.4, J10.8
AREF: A1.AREF, J7.8
BLOWER_ENABLE: A1.D22, J8.4, R10.2
BLOWER_TACH: A1.A0, J5.1, R11.2
CANR: A1.CANR (CANRX), J4.7
CANT: A1.CANT (CANTX), J4.8
CIPO: A1.MISO (SPI_MISO), CIPO1.1, Q6.2 (S), R51.2, R60.2, R62.2
COPI: A1.MOSI (SPI_MOSI), COPI1.1, Q8.2 (S), R6.1, R53.2, R65.2
D0: A1.D0 (D0/RX0), J6.1
D1: A1.D1 (D1/TX0), J6.2
D23: A1.D23, J8.3
D25: A1.D25, J8.5
D27: A1.D27, J8.7
D29: A1.D29, J8.9
D31: A1.D31, J8.11
D32: A1.D32, J8.14, Q5.2 (S), R55.2, R61.2
D37: A1.D37, J8.17, R91.2
D38: A1.D38, J8.20, R8.2
D39: A1.D39, C1.1, J1.1, J8.19
D40: A1.D40, J8.22
D41: A1.D41, J8.21
D42: A1.D42, J8.24
D43: A1.D43, J8.23
D44: A1.D44, J8.26
D45: A1.D45, J8.25
D46: A1.D46, J8.28
D47: A1.D47, J8.27
D48: A1.D48, J8.30
D49: A1.D49, J8.29
D50: A1.D50, J8.32
D51: A1.D51, J8.31, R9.1
D52: A1.D52 (D52_CS2), J8.34
D53: A1.D53, J8.33
DAC0: A1.DAC0, J4.5
DAC1: A1.DAC1, J4.6
GND: A1.GND1 (GND), A1.GND2 (GND), A1.GND3 (GND), A1.GND4 (SPI_GND), A1.GND5 (GND), A1.GND6 (GND), C1.2, C2.2, C3.2, C4.2, C5.2, C6.2, C7.2, C8.2, C9.2, C10.2, C11.2, C12.2, C13.2, C14.2, C15.2, C16.2, C17.2, C18.2, C19.2, C20.2, C21.2, C22.1, D1.2 (A), D2.2 (A), H1.1, H2.1, H3.1, H4.1, H5.1, J1.0 (PAD), J1.3, J1.6, J1.7, J1.8, J1.9, J3.2, J3.3, J7.7, J8.35, J8.36, J9.3, J9.5, J9.7, J9.8, J9.9, J10.6, J10.10, J10.14, J10.16, J10.18, J10.22, J11.2, J12.2, J15.0 (PAD), J15.14, J15.15, J15.16, J15.17, J18.1, J20.1, J21.3, J24.3, JP1.3 (B), JP2.1 (A), JP3.1 (A), JP4.1 (A), JP5.1 (A), JP6.3 (B), JP7.1 (A), JP8.1 (A), JP9.8, JP10.8, JP11.1 (A), JP12.1 (A), JP13.3 (B), JP14.1 (A), JP15.8, JP16.3, JP17.3, JP18.3, JP19.2, JP20.2, JP21.2, Q1.2 (S), Q3.2 (S), Q4.2 (S), R32.1, R43.2, R46.2, R63.1, R81.2, R85.1, R86.1, R87.1, S1.1, S1.2, TP1.1, TP3.1, TP4.1, TP11.1
LOOPBACK13: A1.D36, J8.18, R92.2
unnamed: A1.D4 (D4_CS1), J6.5
unnamed: A1.D10 (D10_CS0), J7.3
unnamed: A1.D14 (D14/TX3), J2.1
unnamed: A1.D15 (D15/RX3), J2.2
unnamed: A1.D16 (D16/TX2), J2.3
unnamed: A1.D17 (D17/RX2), J2.4
unnamed: A1.IORF (IOREF), J3.7
unnamed: A1.RST1 (RESET), J3.6
unnamed: C2.1, J1.5, R8.1
unnamed: C22.2, ISO1.1, ISO2.1, ISO3.1, ISO4.1, ISO5.1, R32.2
unnamed: D1.1 (K), J20.4, Q1.3 (D), R33.2, R34.2, R36.1
unnamed: A1.VIN, J3.1, R76.2, VIN1.1
unnamed: A1.A8, J4.1
unnamed: A1.A9, J4.2
unnamed: A1.A10, J4.3
unnamed: A1.A11, J4.4
unnamed: A1.A1, J5.2
unnamed: A1.A2, J5.3
unnamed: A1.A3, J5.4
unnamed: A1.A4, J5.5
unnamed: A1.A5, J5.6
unnamed: A1.A6, J5.7
unnamed: A1.A7, J5.8
unnamed: A1.D2, J6.3
unnamed: A1.D3, J6.4
unnamed: A1.D6, J6.7
unnamed: A1.D7, J6.8
unnamed: A1.D8, J7.1
unnamed: A1.D11, J7.4
unnamed: A1.D12, J7.5
unnamed: A1.D13, J7.6
unnamed: A1.D24, J8.6
unnamed: A1.D26, J8.8
unnamed: A1.D28, J8.10
unnamed: A1.D30, J8.12
unnamed: J15.18, J19.1
unnamed: J15.19, J19.2
unnamed: J15.20, J19.3
unnamed: J15.21, J19.4
unnamed: J15.22, J19.5
unnamed: J15.23, J19.6
unnamed: J15.24, J19.7
unnamed: JP1.2 (C), R22.1
unnamed: JP2.2 (C), R20.1
unnamed: JP3.2 (C), R19.1
unnamed: JP4.2 (C), R18.1
unnamed: JP5.2 (C), R25.1
unnamed: JP6.2 (C), R24.1
unnamed: JP7.2 (C), R23.1
unnamed: JP8.2 (C), R21.1
unnamed: JP9.2, R18.2
unnamed: JP9.3, R19.2
unnamed: JP9.4, R20.2
unnamed: JP9.5, R22.2
unnamed: JP9.6, TP6.1
unnamed: JP10.2, R21.2
unnamed: JP10.3, R23.2
unnamed: JP10.4, R24.2
unnamed: JP10.5, R25.2
unnamed: JP10.6, TP7.1
unnamed: JP11.2 (C), R29.1
unnamed: JP12.2 (C), R28.1
unnamed: JP13.2 (C), R27.1
unnamed: JP14.2 (C), R26.1
unnamed: JP15.2, R26.2
unnamed: JP15.3, R27.2
unnamed: JP15.4, R28.2
unnamed: JP15.5, R29.2
unnamed: JP15.6, TP8.1
unnamed: JP19.9, R85.2
unnamed: JP20.9, R86.2
unnamed: JP21.9, R87.2
unnamed: Q1.1 (G), R38.1
unnamed: Q2.1 (G), R40.1
unnamed: Q3.3 (D), R40.2, R44.2
unnamed: Q3.1 (G), R45.1
unnamed: Q4.3 (D), R48.1
unnamed: Q4.1 (G), R47.2
unnamed: Q9.3 (D), R69.2, R71.2
unnamed: Q10.3 (D), R70.2, R72.2
unnamed: R39.2, R44.1
unnamed: R60.1, R63.2
ONE_WIRE_TC: A1.D5, J6.6, JP9.1, JP10.1, JP15.1, R83.1
SCL: A1.D21 (D21/SCL), J2.8, Q9.2 (S), R2.1, R16.1, R67.2, R77.1, SCL1.1
SCL1: A1.SCL1, J7.10
SDA: A1.D20 (D20/SDA), J2.7, Q10.2 (S), R4.1, R13.2, R68.2, R78.1, SDA1.1
SDA1: A1.SDA1, J7.9
SPI_SCK: A1.SCK (SPI_SCK), Q7.2 (S), R5.1, R52.2, R64.2, SPI_SCK1.1
SPI_nRST: A1.RST2 (SPI_RESET), S1.3, S1.4
TC_nCS1: A1.D33, J8.13, R7.1
TC_nCS2: A1.D34, J8.16, R3.1
TC_nCS3: A1.D35, J8.15, R1.1
nFAN1_PWM: A1.D9, J7.2, R12.2

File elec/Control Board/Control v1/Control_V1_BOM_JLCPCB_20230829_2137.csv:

Comment,Designator ,Footprint ,JLCPCB Part # 
39pF,"C1, C2, C3, C4, C5, C6, C7, C8, C9, C10, C11, C12, C13, C14, C15, C20, C21",Capacitor_SMD:C_0603_1608Metric_Pad1.08x0.95mm_HandSolder,C107049 
NCE01P30K,Q2,Package_TO_SOT_SMD:TO-252-2,C115991
Conn_02x18_Odd_Even,J8,Connector_PinSocket_2.54mm:PinSocket_2x18_P2.54mm_Vertical,C132131
SWITCH_TACTILE_SPST-NO_0.05A_24V,S1,PubInv_KiCad_PCB:Switch_Tactile_THT_6x6mm,C13828
DB9_Female_MountingHoles,J1,Connector_Dsub:DSUB-9_Female_Horizontal_P2.77x2.84mm_EdgePinOffset4.94mm_Housed_MountingHolesOffset7.48mm,C141882
0.100_2Pin,"J22, J23",Connector_PinHeader_2.54mm:PinHeader_1x02_P2.54mm_Vertical,C168673
DB25_Female_MountingHoles,J15,Connector_Dsub:DSUB-25_Female_Horizontal_P2.77x2.84mm_EdgePinOffset4.94mm_Housed_MountingHolesOffset7.48mm,C190083
4M7,R32,Resistor_SMD:R_0603_1608Metric_Pad0.98x0.95mm_HandSolder,C23163
1R0,"R1, R2, R3, R4, R5, R6, R7, R8, R13, R14, R15, R16, R31, R33, R48, R76, R79, R80, R82, R84, R88",Resistor_SMD:R_0603_1608Metric_Pad0.98x0.95mm_HandSolder,C269434
10K,"R39, R40, R41, R44, R46, R56, R61, R64, R65, R67, R68, R69, R70, R81",Resistor_SMD:R_0603_1608Metric_Pad0.98x0.95mm_HandSolder,C269701
1K,"R18, R19, R20, R21, R22, R23, R24, R25, R26, R27, R28, R29, R36, R37, R38, R42, R45, R47, R54, R57, R58, R62",Resistor_SMD:R_0603_1608Metric_Pad0.98x0.95mm_HandSolder,C269704
4K7,"R77, R78, R83",Resistor_SMD:R_0603_1608Metric_Pad0.98x0.95mm_HandSolder,C269713
Conn_01x08,"J2, J4, J5, J6",Connector_PinSocket_2.54mm:PinSocket_1x08_P2.54mm_Vertical,C2894931
Conn_01x08,J3,Connector_PinHeader_2.54mm:PinHeader_1x08_P2.54mm_Vertical,C2894931
Conn_01x10,"J7, J9, J14",Connector_PinSocket_2.54mm:PinSocket_1x10_P2.54mm_Vertical,C2894933
Conn_01x05,J17,Connector_PinHeader_2.54mm:PinHeader_1x05_P2.54mm_Vertical,C2897368
Conn_01x04,"J16, J18, J24",Connector_PinHeader_2.54mm:PinHeader_1x04_P2.54mm_Vertical,C2905415
Conn_01x04,J20,Connector_PinHeader_2.54mm:PinHeader_1x04_P2.54mm_Vertical,C2905415
Conn_01x07,J19,Connector_PinHeader_2.54mm:PinHeader_1x07_P2.54mm_Vertical,C2932672
RJ12_6P6C_HORZ,J21,PubInv_KiCad_PCB:RJ12_Amphenol_54601,C305981
39R,"R71, R72",Resistor_SMD:R_0603_1608Metric_Pad0.98x0.95mm_HandSolder,C325713
10nF,C22,Capacitor_SMD:C_0603_1608Metric_Pad1.08x0.95mm_HandSolder,C389113
BSS138,"Q1, Q3, Q4",Package_TO_SOT_SMD:SOT-23,C400505
BSS138,"Q5, Q6, Q7, Q8, Q9, Q10",Package_TO_SOT_SMD:SOT-23,C400505
1uF,"C16, C17, C18, C19",Capacitor_SMD:C_0603_1608Metric_Pad1.08x0.95mm_HandSolder,C91183
Screw_Terminal_01x02,"J11, J12, J13, J25",TerminalBlock_TE-Connectivity:TerminalBlock_TE_282834-2_1x02_P2.54mm_Horizontal,C918120

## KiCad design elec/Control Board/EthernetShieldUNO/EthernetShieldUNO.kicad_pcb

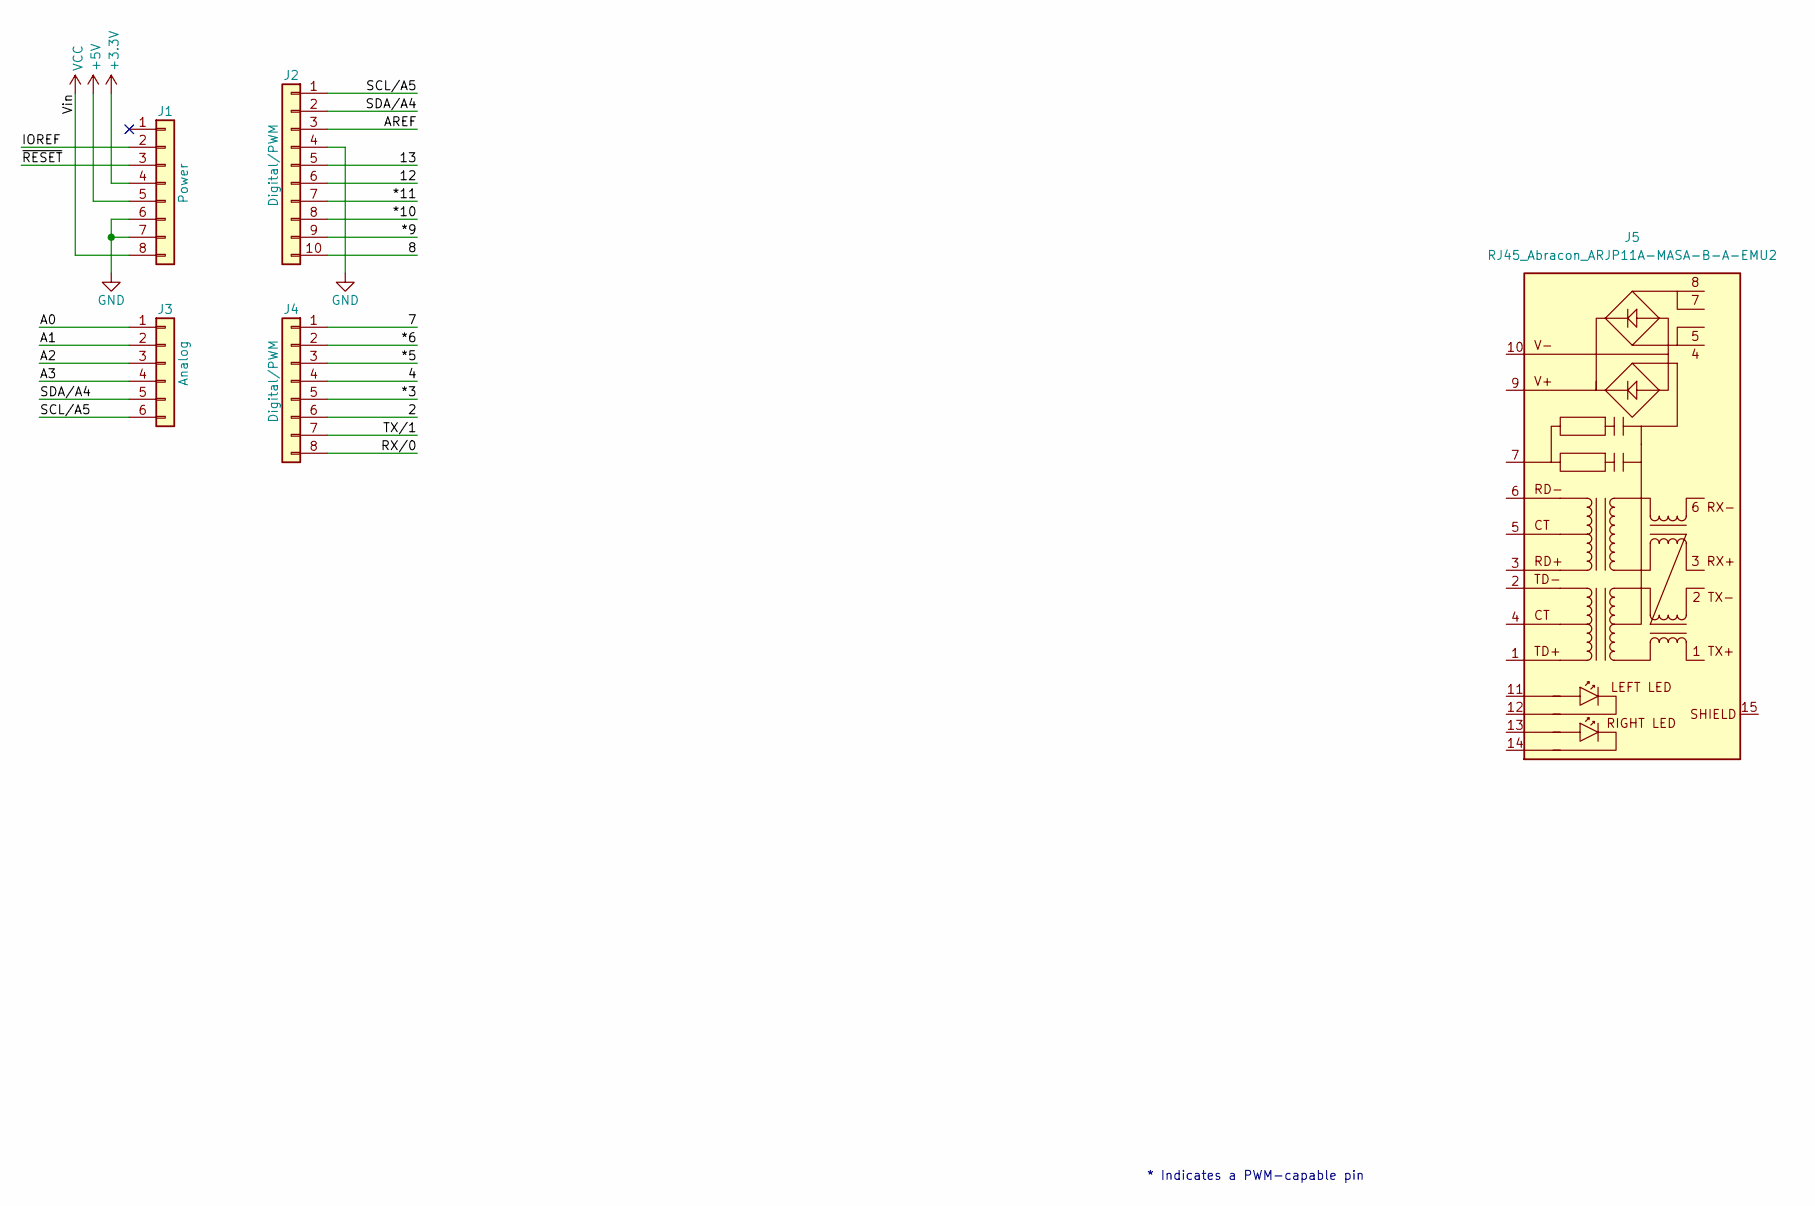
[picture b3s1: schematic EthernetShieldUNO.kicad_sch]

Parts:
J1: Power; PinSocket_1x08_P2.54mm_Vertical
J2: Digital/PWM; PinSocket_1x10_P2.54mm_Vertical
J3: Analog; PinSocket_1x06_P2.54mm_Vertical
J4: Digital/PWM; PinSocket_1x08_P2.54mm_Vertical
J5: RJ45_Abracon_ARJP11A-MASA-B-A-EMU2; RJ45_Abracon_ARJP11A-MA_Horizontal

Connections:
+3V3: J1.4
+5V: J1.5
/2: J4.6
/4: J4.4
/7: J4.1
/8: J2.10
/12: J2.6
/13: J2.5
/*3: J4.5
/*5: J4.3
/*6: J4.2
/*9: J2.9
/*10: J2.8
/*11: J2.7
/A0: J3.1
/A1: J3.2
/A2: J3.3
/A3: J3.4
/AREF: J2.3
/IOREF: J1.2
/RX/0: J4.8
/SCL/A5: J2.1, J3.6
/SDA/A4: J2.2, J3.5
/TX/1: J4.7
/~RESET: J1.3
GND: J1.6, J1.7, J2.4
VCC: J1.8

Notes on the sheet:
* Indicates a PWM-capable pin

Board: 2 copper layers, 9 parts (0 on the bottom side), 3 nets, no tracks yet.

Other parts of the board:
MH1, MH2, MH3, MH4: MountingHole_3.2mm

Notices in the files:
elec/Control Board/Control v1/README.md:
License & Legal:
Copyright 2017-2023, [Nicholas Parks Young](https://github.com/Alarm-Siren).
Except as otherwise noted, all content of this library is licensed under the
[Creative Commons Attribution-ShareAlike 4.0 International License](https://creativecommons.org/licenses/by-sa/4.0/), with the following additional exception: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
CC BY-SA 4.0
CC BY-SA-NC 4.0
elec/Control Board/Control v1/Control v1.kicad_pcb:
CERN Open Hardware License Version 2 - Strongly Reciprocal
